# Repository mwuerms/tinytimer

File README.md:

# tinytimer

TinyTimer is a small electronic device (using Attiny404) on a pcb, which offers 4 simple timers and each a led to gently inform the user of an alarm.

## User interface

The led shows the status of the timer
+ off (LED off)
+ running (gently fade in 1 - 2 s)
+ pause (double blink shortly in 1 - 2 s)
+ alarm (blink wildly for 20 s)

With the button, the user can control the timer
+ start
+ pause/resume
+ stop/abort

Each timer has a fixed timeout, eg.
1. 3 min (tea)
2. 5 min
3. 10 min
4. 25 min

Each timer can run independently from all others.

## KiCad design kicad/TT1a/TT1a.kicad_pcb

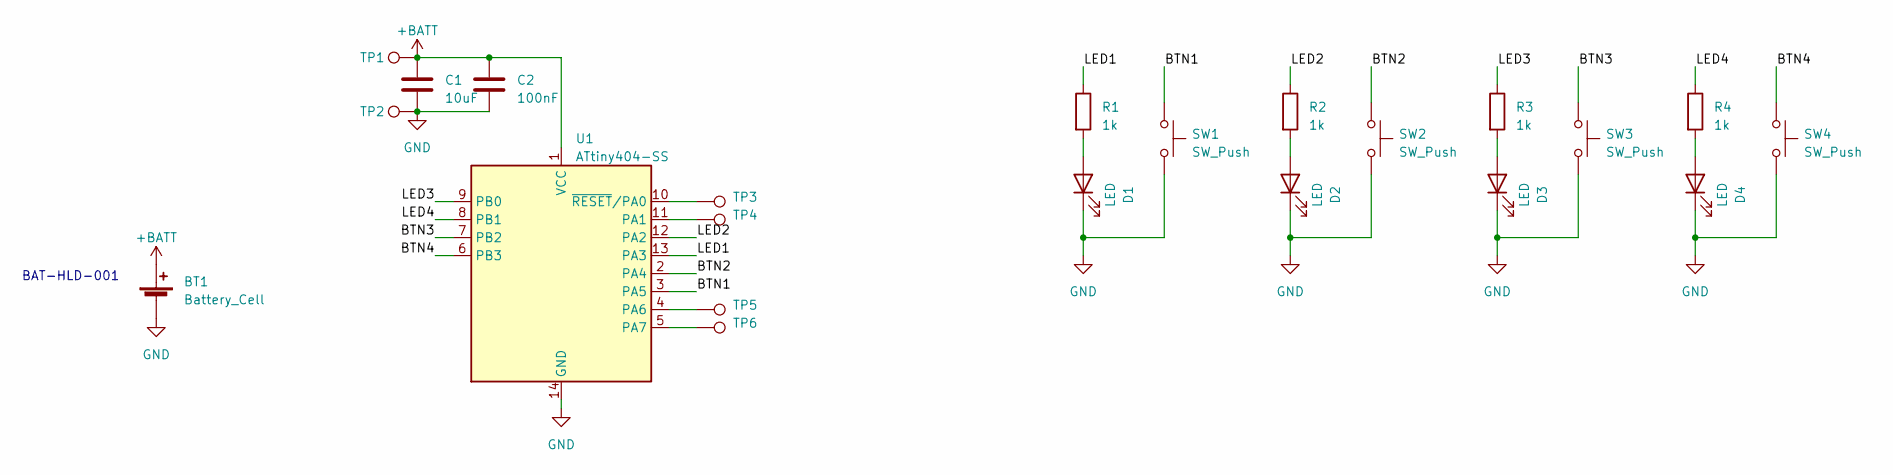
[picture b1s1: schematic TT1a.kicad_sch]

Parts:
BT1: Battery_Cell; BAT-HLD-001
C1: 10uF; C_0805_2012Metric
C2: 100nF; C_0603_1608Metric
D1, D2, D3, D4: LED; LED_0603_1608Metric
R1, R2, R3, R4: 1k; R_0603_1608Metric
SW1, SW2, SW3, SW4: SW_Push; PTS526_button
TP1, TP2, TP3, TP4, TP5, TP6: TestPoint; TestPoint_Pad_D1.0mm
U1: ATtiny404-SS; SOIC-14_3.9x8.7mm_P1.27mm

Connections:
+BATT: BT1.1 (+), C1.1, C2.1, TP1.1, U1.1 (VCC)
/BTN1: SW1.1, U1.3 (PA5)
/BTN2: SW2.1, U1.2 (PA4)
/BTN3: SW3.1, U1.7 (PB2)
/BTN4: SW4.1, U1.6 (PB3)
/LED1: R1.1, U1.13 (PA3)
/LED2: R2.1, U1.12 (PA2)
/LED3: R3.1, U1.9 (PB0)
/LED4: R4.1, U1.8 (PB1)
GND: BT1.2 (-), C1.2, C2.2, D1.1 (K), D2.1 (K), D3.1 (K), D4.1 (K), SW1.2, SW2.2, SW3.2, SW4.2, TP2.1, U1.14 (GND)
unnamed: D1.2 (A), R1.2
unnamed: D2.2 (A), R2.2
unnamed: D3.2 (A), R3.2
unnamed: D4.2 (A), R4.2
unnamed: TP4.1, U1.11 (PA1)
unnamed: TP5.1, U1.4 (PA6)
unnamed: TP6.1, U1.5 (PA7)
unnamed: TP3.1, U1.10 (~RESET/PA0)

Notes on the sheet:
BAT-HLD-001

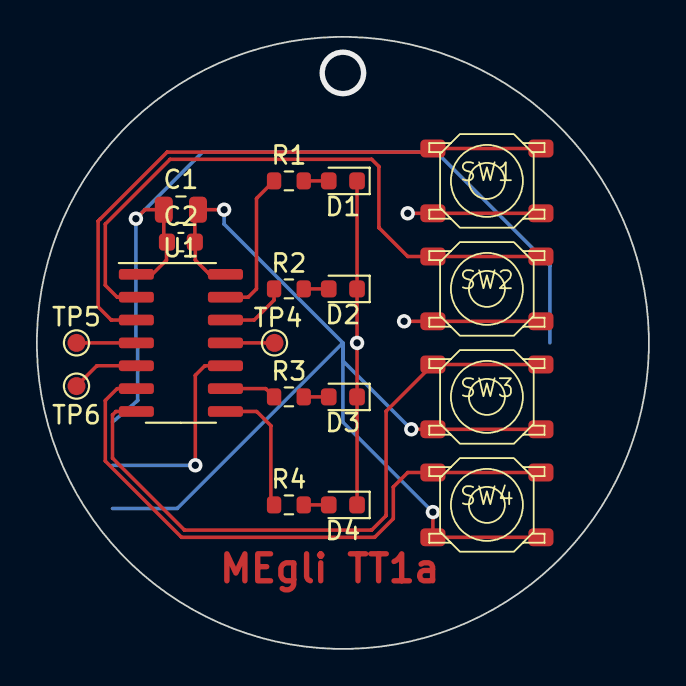
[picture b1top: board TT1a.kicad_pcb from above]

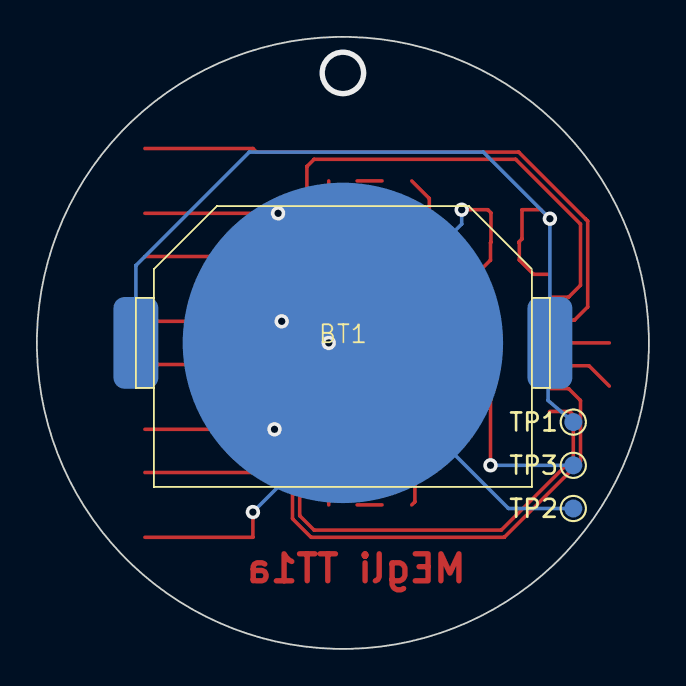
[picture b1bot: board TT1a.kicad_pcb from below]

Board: 2 copper layers, 34.0 x 34.0 mm, 22 parts (4 on the bottom side), 18 nets.

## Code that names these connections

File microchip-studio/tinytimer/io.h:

/**
 * Martin Egli
 * 2023-03-21
 * define io
 */

#ifndef _IO_H_
#define _IO_H_

#include <avr/io.h>

// LED1: PA3
#define LED1_PORT	PORTA
#define LED1_PIN	3
#define LED1_PIN_BV	_BV(LED1_PIN)
// LED2: PA2
#define LED2_PORT	PORTA
#define LED2_PIN	2
#define LED2_PIN_BV	_BV(LED2_PIN)
// LED3: PB0
#define LED3_PORT	PORTB
#define LED3_PIN	0
#define LED3_PIN_BV	_BV(LED3_PIN)
// LED4: PB1
#define LED4_PORT	PORTB
#define LED4_PIN	1
#define LED4_PIN_BV	_BV(LED4_PIN)

// BUTTON1: PA5
#define BUTTON1_PORT	PORTA
#define BUTTON1_PIN		5
#define BUTTON1_PIN_BV	_BV(BUTTON1_PIN)
#define BUTTON1_PIN_CTRL	PIN##5##CTRL
// BUTTON2: PA4
#define BUTTON2_PORT	PORTA
#define BUTTON2_PIN		4
#define BUTTON2_PIN_BV	_BV(BUTTON2_PIN)
#define BUTTON2_PIN_CTRL	PIN##4##CTRL
// BUTTON3: PB2
#define BUTTON3_PORT	PORTB
#define BUTTON3_PIN		2
#define BUTTON3_PIN_BV	_BV(BUTTON2_PIN)
#define BUTTON3_PIN_CTRL	PIN##2##CTRL
// BUTTON4: PB3
#define BUTTON4_PORT	PORTB
#define BUTTON4_PIN		3
#define BUTTON4_PIN_BV	_BV(BUTTON4_PIN)
#define BUTTON4_PIN_CTRL	PIN##3##CTRL

// DBG1: PA1 (TxD, alternate)
#define DBG1_PORT	    PORTA
#define DBG1_PIN		1
#define DBG1_PIN_BV		_BV(DBG1_PIN)
#define DBG1_DIR_OUT()  DBG1_PORT.DIRSET = DBG1_PIN_BV
#define DBG1_PIN_SET()  DBG1_PORT.OUTSET = DBG1_PIN_BV
#define DBG1_PIN_CLR()  DBG1_PORT.OUTCLR = DBG1_PIN_BV

// DBG2: PA6
#define DBG2_PORT	    PORTA
#define DBG2_PIN		6
#define DBG2_PIN_BV		_BV(DBG2_PIN)
#define DBG2_DIR_OUT()  DBG2_PORT.DIRSET = DBG2_PIN_BV
#define DBG2_PIN_SET()  DBG2_PORT.OUTSET = DBG2_PIN_BV
#define DBG2_PIN_CLR()  DBG2_PORT.OUTCLR = DBG2_PIN_BV

// DBG3: PA7
#define DBG3_PORT	    PORTA
#define DBG3_PIN		7
#define DBG3_PIN_BV		_BV(DBG3_PIN)
#define DBG3_DIR_OUT()  DBG3_PORT.DIRSET = DBG3_PIN_BV
#define DBG3_PIN_SET()  DBG3_PORT.OUTSET = DBG3_PIN_BV
#define DBG3_PIN_CLR()  DBG3_PORT.OUTCLR = DBG3_PIN_BV

#endif

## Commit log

2023-03-18 started pcb TT1a
2023-03-18 Schematic done but components arent done yet Bat1: use BAT-HLD-001 Switches: use PTS526 SK15 SMTR2 LFS update library for that
2023-03-19 TT1a: changed footprints for Bat + Buttons
2023-03-19 pcb TT1a done
2023-03-21 timytimer started project
2023-03-21 README: added short description + user interface
2023-03-22 tinytimer added rtc, leds, pwr added led animation
2023-03-25 leds: tested leds_ShowRunning() and leds_ShowAlarm() successfully
2023-03-25 leds: variables renamed docs: some calculations added
2023-03-25 rtc testing: needs to be aktivated right at the start
2023-03-26 rtc: add rtc_timer_process_list to handle all the different timers in one rtc done for the moment, needs some serious testing though
2023-03-26 button started with ISR
2023-03-27 button: 1st version done, may work but this way is not at all prefered
2023-03-27 button: much better now: emit event when ISR gets called and save button state there, then call button_ProcessEvent() from foreground
2023-03-27 rtc: process events from fifo/list in ISR
2023-03-28 all done, now do some testing
2023-04-01 dbg pins: added debug output for testing, tested multiple active rtc_timers: worked
2023-04-01 leds: added pause smoother "running" animation (better sinus, not so bright, 0 at the end) and more testing
2023-04-12 uart, dbguart: added uart txd functionality for debug purpose (untested)
2023-04-14 uart worked, but wont now :-(
2023-04-19 found "bug" (may be not, rather missunderstanding) in uart, send any character after Init, so the while-loop for status wont dead-lock
2023-04-19 works basically, but with some strange behaviour on button3 and when no led is running
